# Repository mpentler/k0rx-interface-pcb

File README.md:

# k0rx-interface-pcb
A PCB implementation of an audio data mode interface designed by K0RX, David Andersen

Original circuit here: https://k0rx.com/blog/2017/11/baofeng.html

I made this up into a small 4x4cm PCB to replace a horrible stripboard prototype. I'm releasing the Gerber files and the KiCad project in case anyone wants to have a play. The project has now been upgraded to be compatible with KiCad V6, but some things may need reconnecting. Sorry. Same for V7.

There are more complex interfaces available to make or buy but I loved the simplicity of David's design. A small enclosure could be made for a box, and I've included an example of this in FreeCAD format also.

I had to change some resistors in my implementation as David mentions, and I totally missed out the potentiometer, opting for a single 2k2 resistor (edit 2023: my output is way hot - clearly needs the resistor value increasing). I also added a hard switch for toggling Tx/Rx as well as the optocoupler. I am only using a single audio channel as David does, so you can either leave the other one hanging or send to ground I guess. The Rx resistor may need some adjustment, see what level works for you (breadboard it and test, perhaps). I will change this to potentiometers for a V3 as different radios and PCs can vary wildly in level.

An improvement you may want to add is a proper connector for the radio cable rather than cutting the end off a cable and soldering it directly. Especially if mounting it in a box.

This interface works great for me for SSTV & APRS work and for general audio recording from the radio. The total cost of all of the parts (including PCB fabbing from JLCPCB) is around £15, the most expensive parts being the cables.

# Parts List

* R1 - High value for receive audio, typically 62k-100k Ohm
* R2 - 2.2k Ohm for transmit audio (this may need to be higher also, again, experimentation is useful)
* R3 - 330 Ohm
* C1 - 0.1uF ceramic capacitor
* T1 - 1:1 600 Ohm transformer
* U1 - PC817 Optocoupler to pull PTT to GND
* SW1 - SPDT slide switch for hard TX/RX switching
* J1 - TRRS jack socket
* J2 - Pin header or bare pads - Audio out, GND
* J3 - Pin header or bare pads - Audio in, PTT
* J4 - Pin header or bare pads - RS232

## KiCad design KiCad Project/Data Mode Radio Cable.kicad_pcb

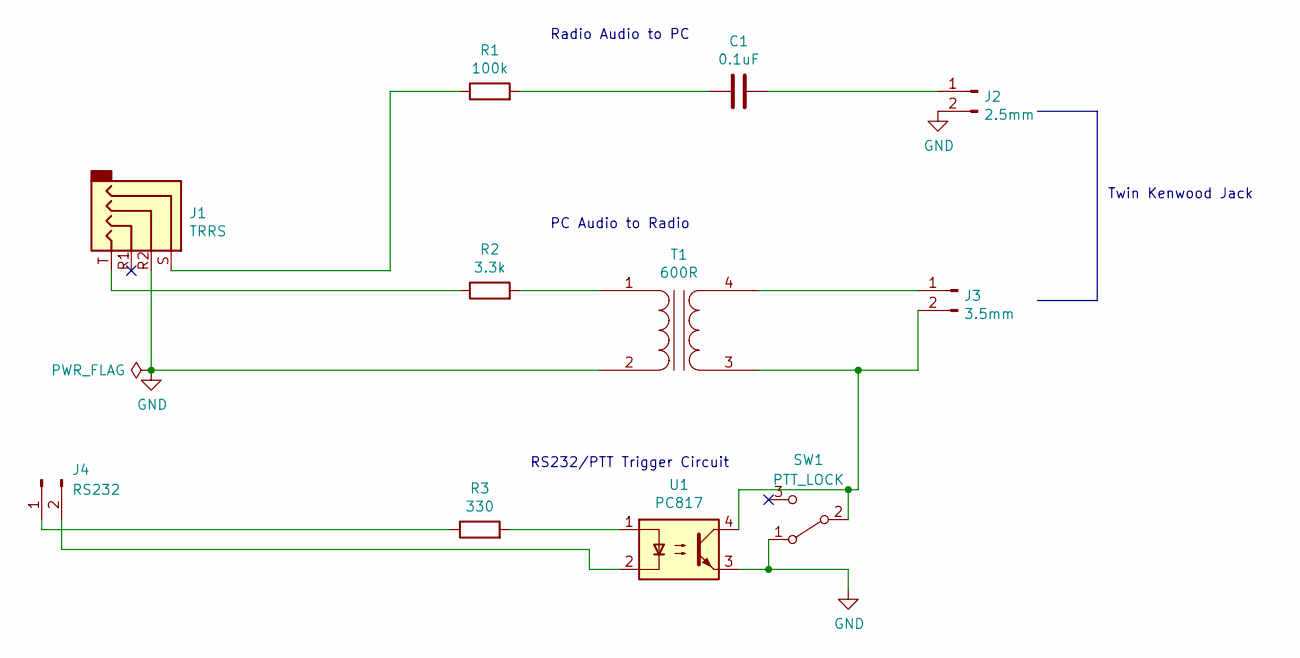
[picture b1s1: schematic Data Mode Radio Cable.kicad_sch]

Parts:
C1: 0.1uF; C_Disc_D5.0mm_W2.5mm_P5.00mm
J1: TRRS; TRRS-PJ-320A
J2: 2.5mm; PinHeader_1x02_P2.54mm_Vertical
J3: 3.5mm; PinHeader_1x02_P2.54mm_Vertical
J4: RS232; PinHeader_1x02_P2.54mm_Vertical
R1: 100k; R_Axial_DIN0207_L6.3mm_D2.5mm_P7.62mm_Horizontal
R2: 3.3k; R_Axial_DIN0207_L6.3mm_D2.5mm_P7.62mm_Horizontal
R3: 330; R_Axial_DIN0207_L6.3mm_D2.5mm_P7.62mm_Horizontal
SW1: PTT_LOCK; SPDT_Right_Angled_Switch
T1: 600R; 1-1_Audio_Transformer_600_ohm
U1: PC817; DIP-4_W7.62mm

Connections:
GND: J1.R2, J2.2, SW1.1 (A), T1.2 (AB), U1.3
unnamed: C1.1, R1.2
unnamed: C1.2, J2.1
unnamed: J1.S, R1.1
unnamed: J1.T, R2.1
unnamed: J3.1, T1.4 (SB)
unnamed: J3.2, SW1.2 (B), T1.3 (SA), U1.4
unnamed: J4.1, R3.1
unnamed: J4.2, U1.2
unnamed: R2.2, T1.1 (AA)
unnamed: R3.2, U1.1

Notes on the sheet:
RS232/PTT Trigger Circuit
Twin Kenwood Jack
PC Audio to Radio
Radio Audio to PC

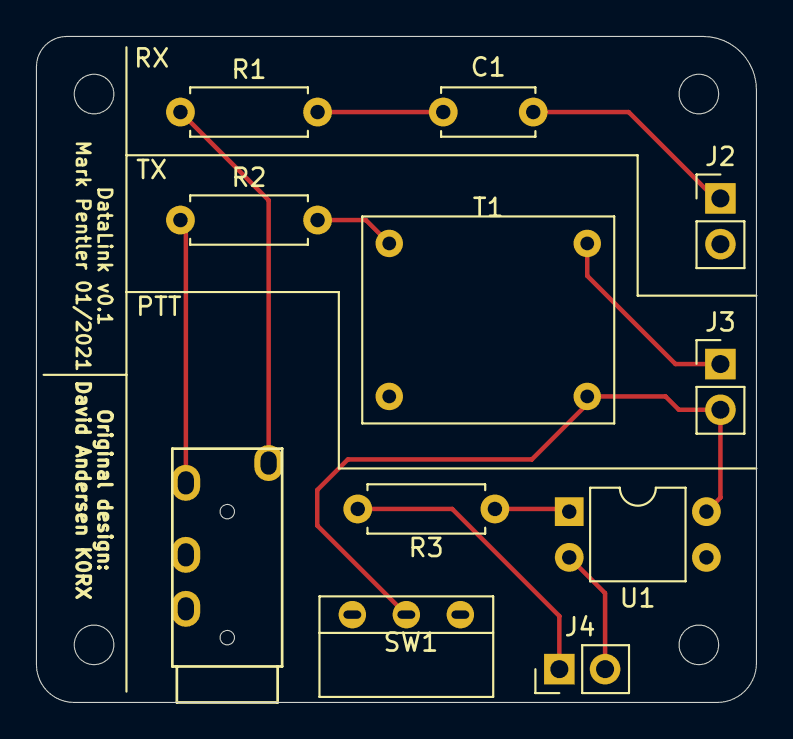
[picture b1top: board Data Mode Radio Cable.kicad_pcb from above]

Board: 2 copper layers, 40.0 x 37.0 mm, 11 parts (0 on the bottom side), 11 nets.

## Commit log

2021-05-22 Update README.md
    Just some initial details before I upload the rest of it next week.
2021-05-22 Initial upload of project files
    Initial commit, I am quite stupid when it comes to KiCad so I don't quite know how to include the extra footprints and models I used yet...
2021-05-22 Delete fp-info-cache
    Woops - guess this isn't needed
2021-05-22 Update README.md
    Added a photo of the board (if my markdown has worked...)
2022-01-15 Update README.md
    Added parts list
2022-01-21 Delete KiCad Project directory
    Preps for V6 files
2022-01-21 V6 file upgrade
    Replacing this folder with V6 files, hopefully all still works OK!
2022-01-21 3d model folder
    add custom models to project
2022-01-21 Custom footprint addition
    Copying library folder over now I know how to do them per-project
2022-01-21 Add files via upload
    Replaced project files with ones pointing to new per-project footprints
2022-01-21 Delete Data Mode Radio Cable.net
    Seems to be no longer needed in Kicad V6, all transparent between the apps
